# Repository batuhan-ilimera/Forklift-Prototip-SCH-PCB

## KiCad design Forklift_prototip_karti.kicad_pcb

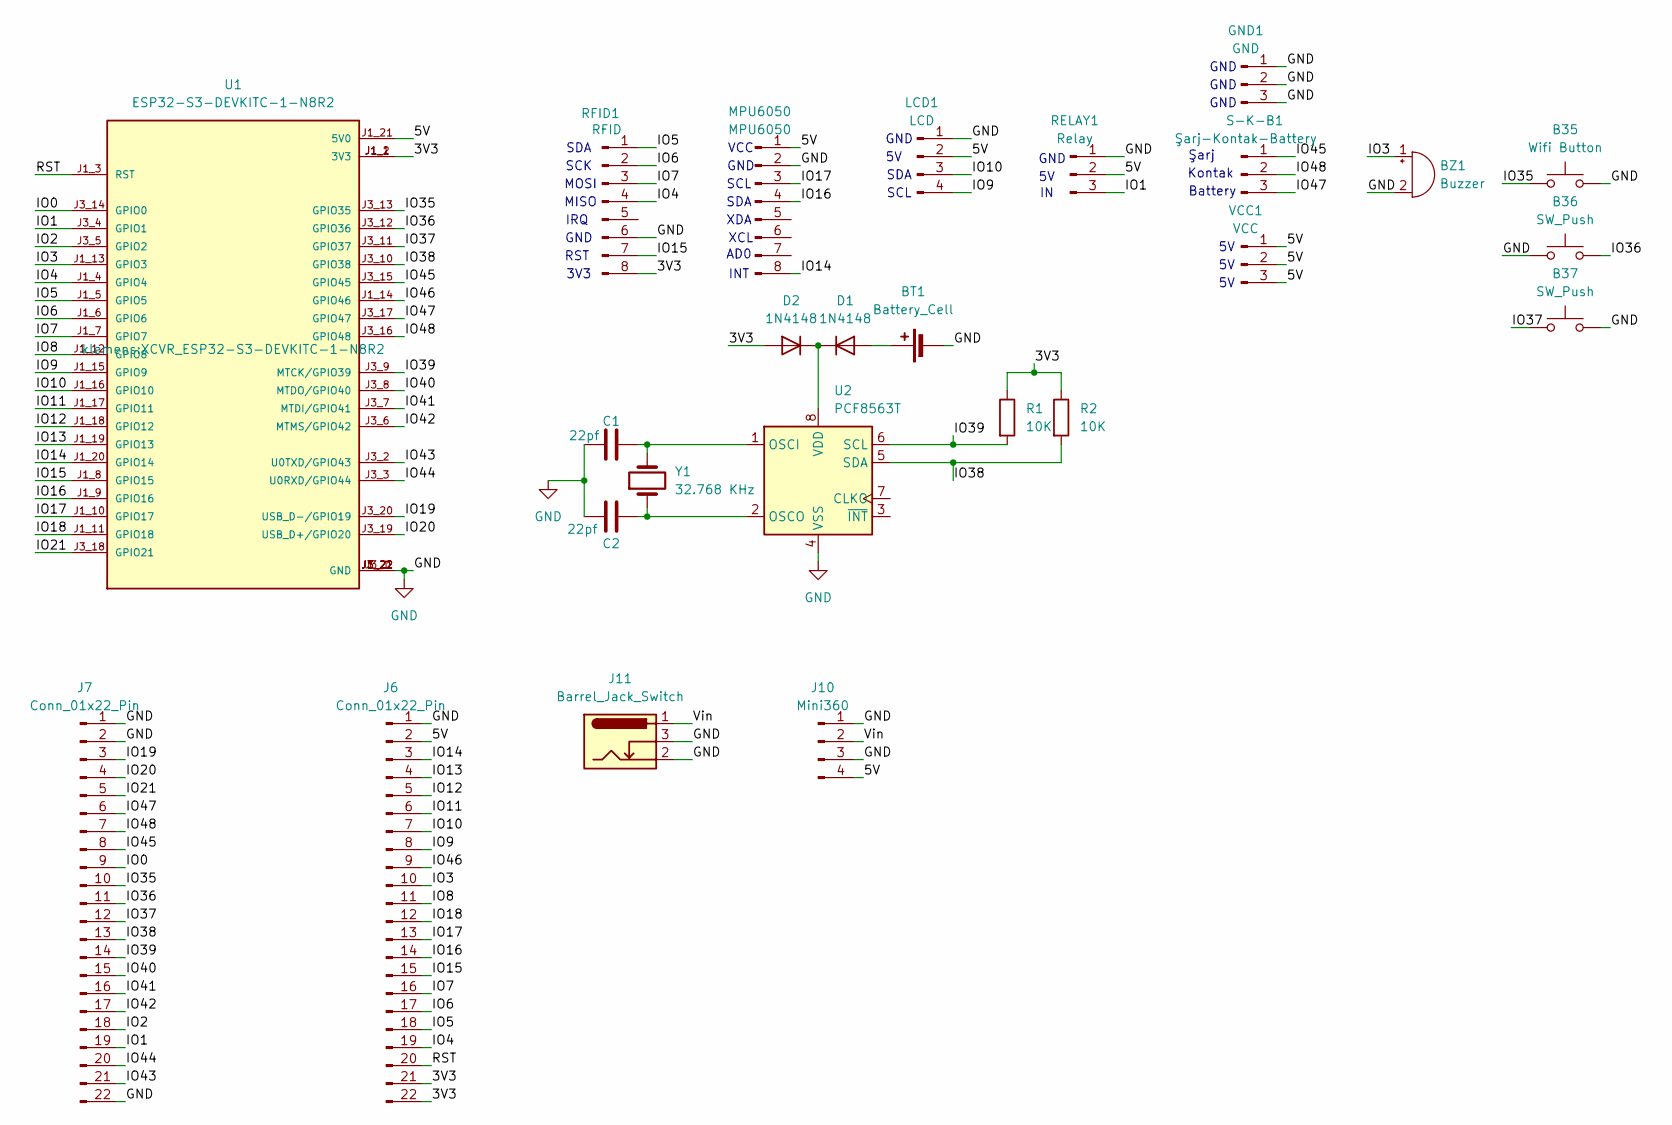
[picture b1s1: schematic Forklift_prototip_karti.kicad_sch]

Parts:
B35: Wifi Button; SW_SPST_PTS645
B36, B37: SW_Push; SW_SPST_PTS645
BT1: Battery_Cell; BatteryHolder_MYOUNG_BS-07-A1BJ001_CR2032
BZ1: Buzzer; Buzzer_12x9.5RM7.6
C1, C2: 22pf; C_Disc_D3.0mm_W1.6mm_P2.50mm
D1, D2: 1N4148; D_DO-35_SOD27_P7.62mm_Horizontal
GND1: GND; PinHeader_1x03_P2.54mm_Vertical
J6, J7: Conn_01x22_Pin; PinHeader_1x22_P2.54mm_Vertical
J10: Mini360; mini360
J11: Barrel_Jack_Switch; BarrelJack_GCT_DCJ200-10-A_Horizontal
LCD1: LCD; PinHeader_1x04_P2.54mm_Vertical
MPU6050: MPU6050; PinHeader_1x08_P2.54mm_Vertical
R1, R2: 10K; R_0603_1608Metric_Pad0.98x0.95mm_HandSolder
RELAY1: Relay; PinHeader_1x03_P2.54mm_Vertical
RFID1: RFID; PinHeader_1x08_P2.54mm_Vertical
S-K-B1: Şarj-Kontak-Battery; PinHeader_1x03_P2.54mm_Vertical
U1: ESP32-S3-DEVKITC-1-N8R2; XCVR_ESP32-S3-DEVKITC-1-N8R2; PARTREV V1
U2: PCF8563T; SOIC-8_3.9x4.9mm_P1.27mm
VCC1: VCC; PinHeader_1x03_P2.54mm_Vertical
Y1: 32.768 KHz; Crystal_DS26_D2.0mm_L6.0mm_Horizontal_1EP_style1

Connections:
/3V3: D2.2 (A), J6.21, J6.22, R1.1, R2.1, RFID1.8, U1.J1_1 (3V3), U1.J1_2 (3V3)
/5V: J6.2, J10.4, LCD1.2, MPU6050.1, RELAY1.2, U1.J1_21 (5V0), VCC1.1, VCC1.2, VCC1.3
/IO0: J7.9, U1.J3_14 (GPIO0)
/IO1: J7.19, RELAY1.3, U1.J3_4 (GPIO1)
/IO2: J7.18, U1.J3_5 (GPIO2)
/IO3: BZ1.1 (+), J6.10, U1.J1_13 (GPIO3)
/IO4: J6.19, RFID1.4, U1.J1_4 (GPIO4)
/IO5: J6.18, RFID1.1, U1.J1_5 (GPIO5)
/IO6: J6.17, RFID1.2, U1.J1_6 (GPIO6)
/IO7: J6.16, RFID1.3, U1.J1_7 (GPIO7)
/IO8: J6.11, U1.J1_12 (GPIO8)
/IO9: J6.8, LCD1.4, U1.J1_15 (GPIO9)
/IO10: J6.7, LCD1.3, U1.J1_16 (GPIO10)
/IO11: J6.6, U1.J1_17 (GPIO11)
/IO12: J6.5, U1.J1_18 (GPIO12)
/IO13: J6.4, U1.J1_19 (GPIO13)
/IO14: J6.3, MPU6050.8, U1.J1_20 (GPIO14)
/IO15: J6.15, RFID1.7, U1.J1_8 (GPIO15)
/IO16: J6.14, MPU6050.4, U1.J1_9 (GPIO16)
/IO17: J6.13, MPU6050.3, U1.J1_10 (GPIO17)
/IO18: J6.12, U1.J1_11 (GPIO18)
/IO19: J7.3, U1.J3_20 (USB_D-/GPIO19)
/IO20: J7.4, U1.J3_19 (USB_D+/GPIO20)
/IO21: J7.5, U1.J3_18 (GPIO21)
/IO35: B35.1, J7.10, U1.J3_13 (GPIO35)
/IO36: B36.2, J7.11, U1.J3_12 (GPIO36)
/IO37: B37.1, J7.12, U1.J3_11 (GPIO37)
/IO38: J7.13, R2.2, U1.J3_10 (GPIO38), U2.5 (SDA)
/IO39: J7.14, R1.2, U1.J3_9 (MTCK/GPIO39), U2.6 (SCL)
/IO40: J7.15, U1.J3_8 (MTDO/GPIO40)
/IO41: J7.16, U1.J3_7 (MTDI/GPIO41)
/IO42: J7.17, U1.J3_6 (MTMS/GPIO42)
/IO43: J7.21, U1.J3_2 (U0TXD/GPIO43)
/IO44: J7.20, U1.J3_3 (U0RXD/GPIO44)
/IO45: J7.8, S-K-B1.1, U1.J3_15 (GPIO45); also elsewhere on the board
/IO46: J6.9, U1.J1_14 (GPIO46)
/IO47: J7.6, S-K-B1.3, U1.J3_17 (GPIO47); also elsewhere on the board
/IO48: J7.7, S-K-B1.2, U1.J3_16 (GPIO48); also elsewhere on the board
/RST: J6.20, U1.J1_3 (RST)
/Vin: J10.2, J11.1
GND: B35.2, B36.1, B37.2, BT1.2 (-), BZ1.2 (-), C1.1, C2.1, GND1.1, GND1.2, GND1.3, J6.1, J7.1, J7.2, J7.22, J10.1, J10.3, J11.2, J11.3, LCD1.1, MPU6050.2, RELAY1.1, RFID1.6, U1.J1_22 (GND), U1.J3_1 (GND), U1.J3_21 (GND), U1.J3_22 (GND), U2.4 (VSS)
unnamed: BT1.1 (+), D1.2 (A)
unnamed: D1.1 (K), D2.1 (K), U2.8 (VDD)
unnamed: C1.2, U2.1 (OSCI), Y1.2
unnamed: C2.2, U2.2 (OSCO), Y1.1

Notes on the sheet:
RST
SCK
SDA
Şarj
INT
XCL
GND
MISO
Battery
IRQ
Kontak
AD0
XDA
3V3
VCC
MOSI
SCL

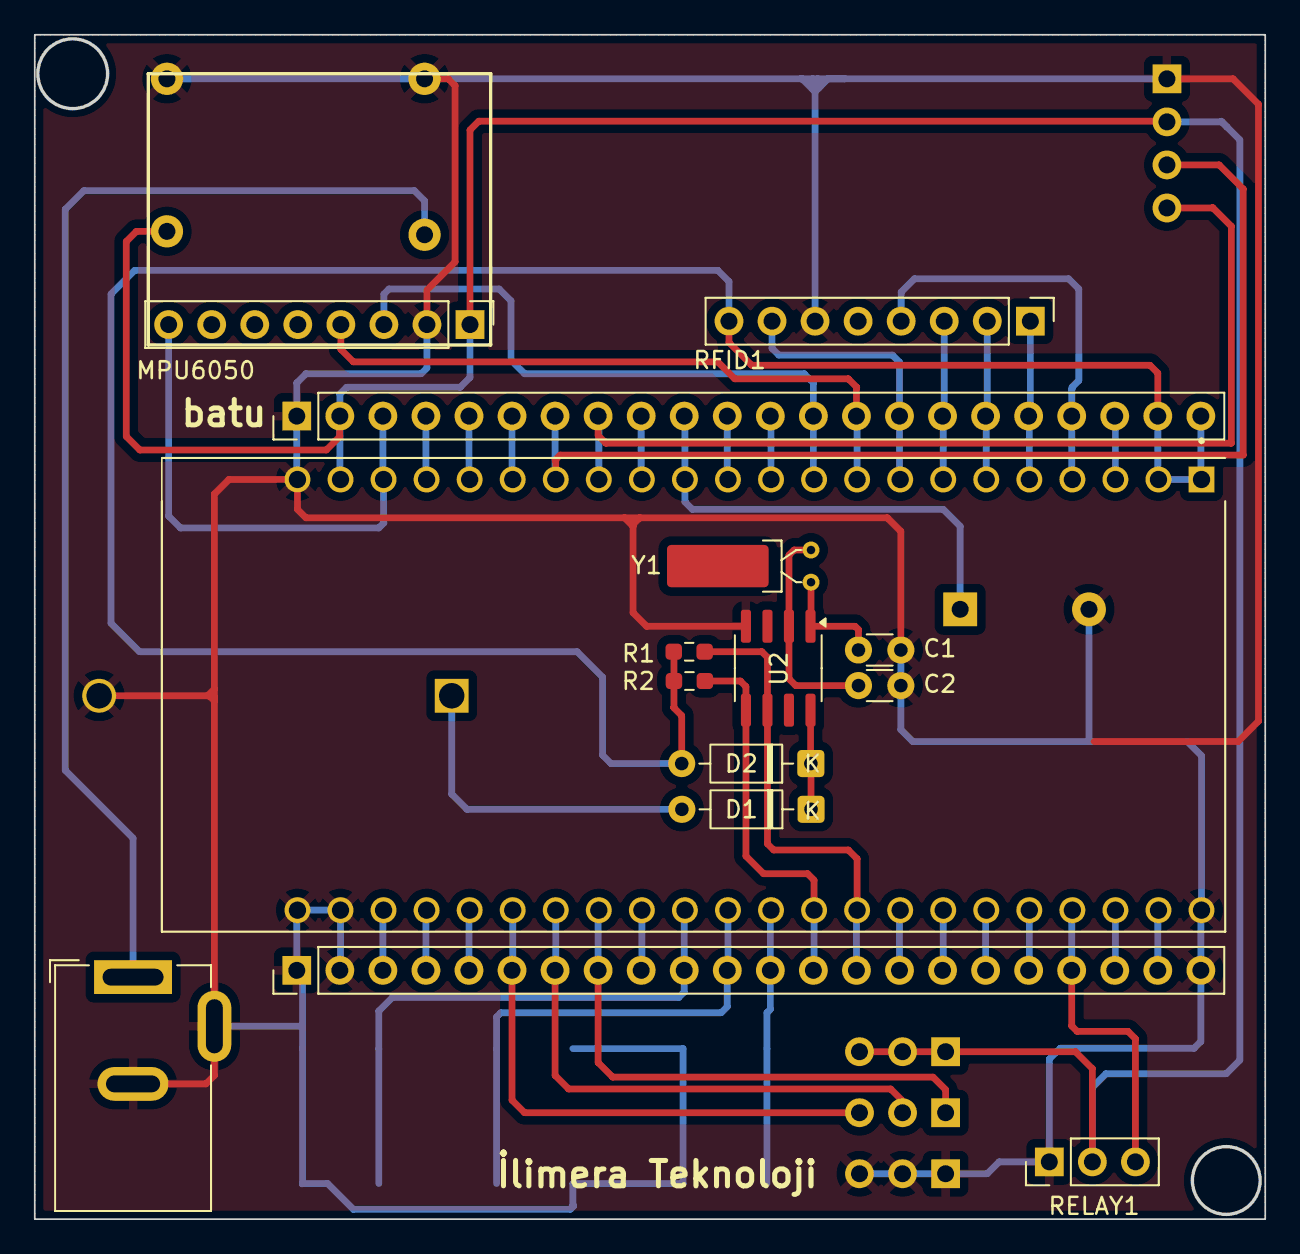
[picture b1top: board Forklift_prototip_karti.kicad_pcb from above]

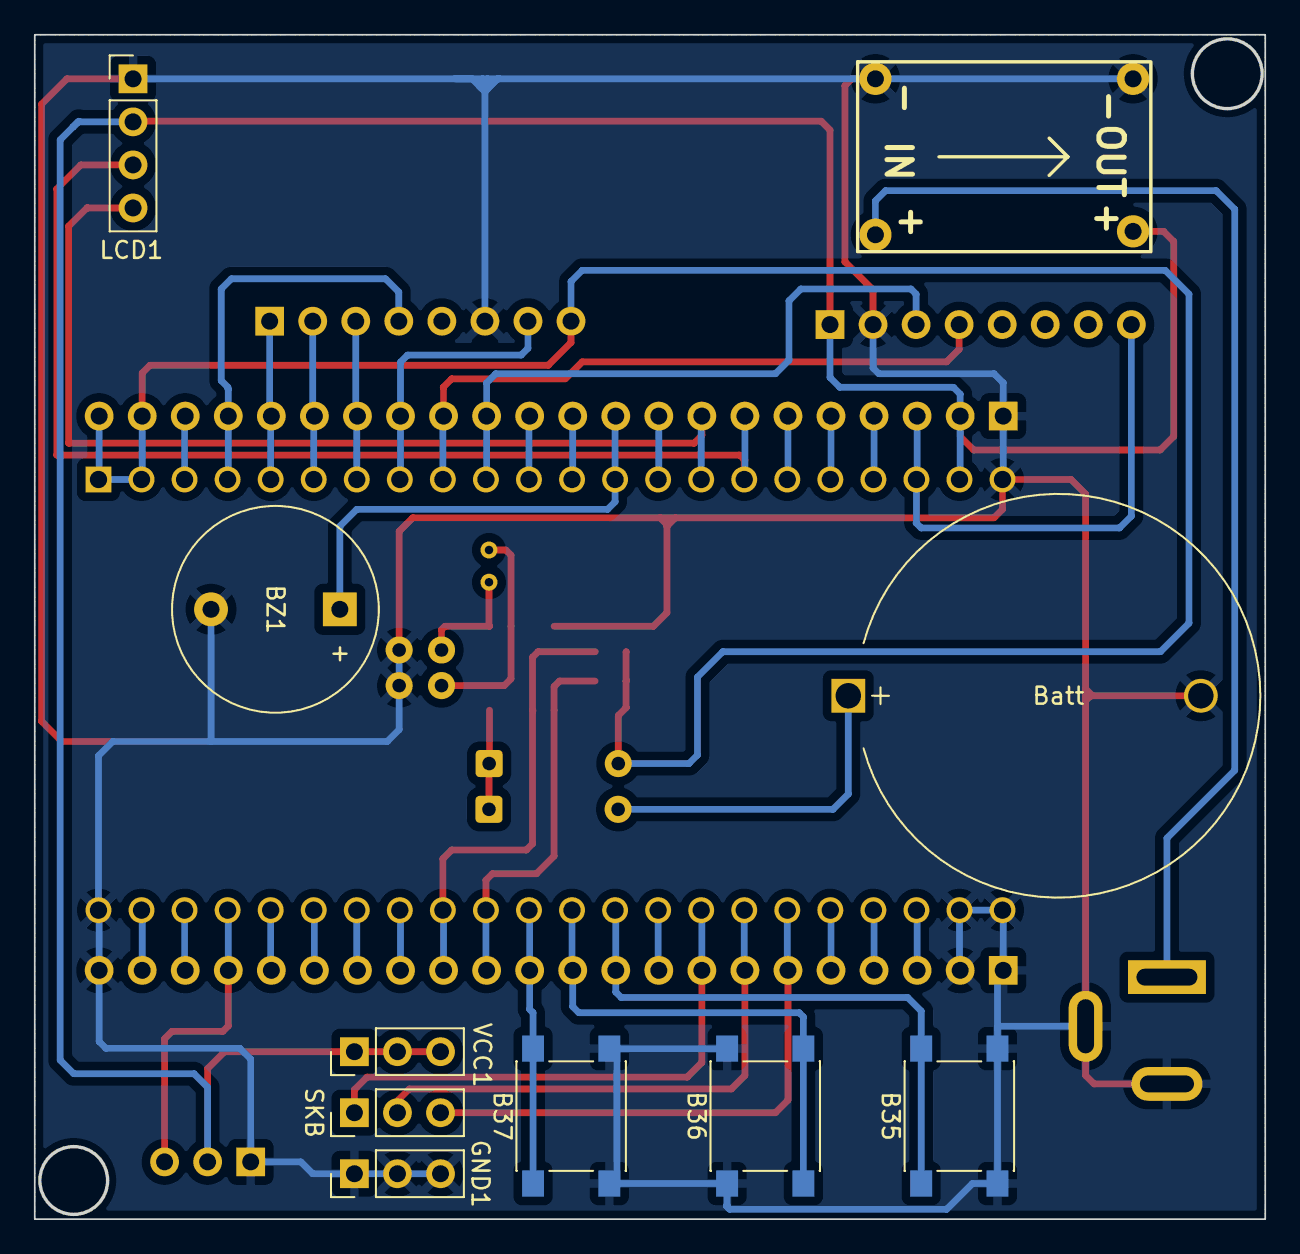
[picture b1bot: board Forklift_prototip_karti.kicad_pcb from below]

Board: 2 copper layers, 72.6 x 69.9 mm, 25 parts (10 on the bottom side), 45 nets.

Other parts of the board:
SKB: Şarj-Kontak-Battery; PinHeader_1x03_P2.54mm_Vertical

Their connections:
/IO45: SKB.1; also elsewhere on the board
/IO47: SKB.3; also elsewhere on the board
/IO48: SKB.2; also elsewhere on the board
